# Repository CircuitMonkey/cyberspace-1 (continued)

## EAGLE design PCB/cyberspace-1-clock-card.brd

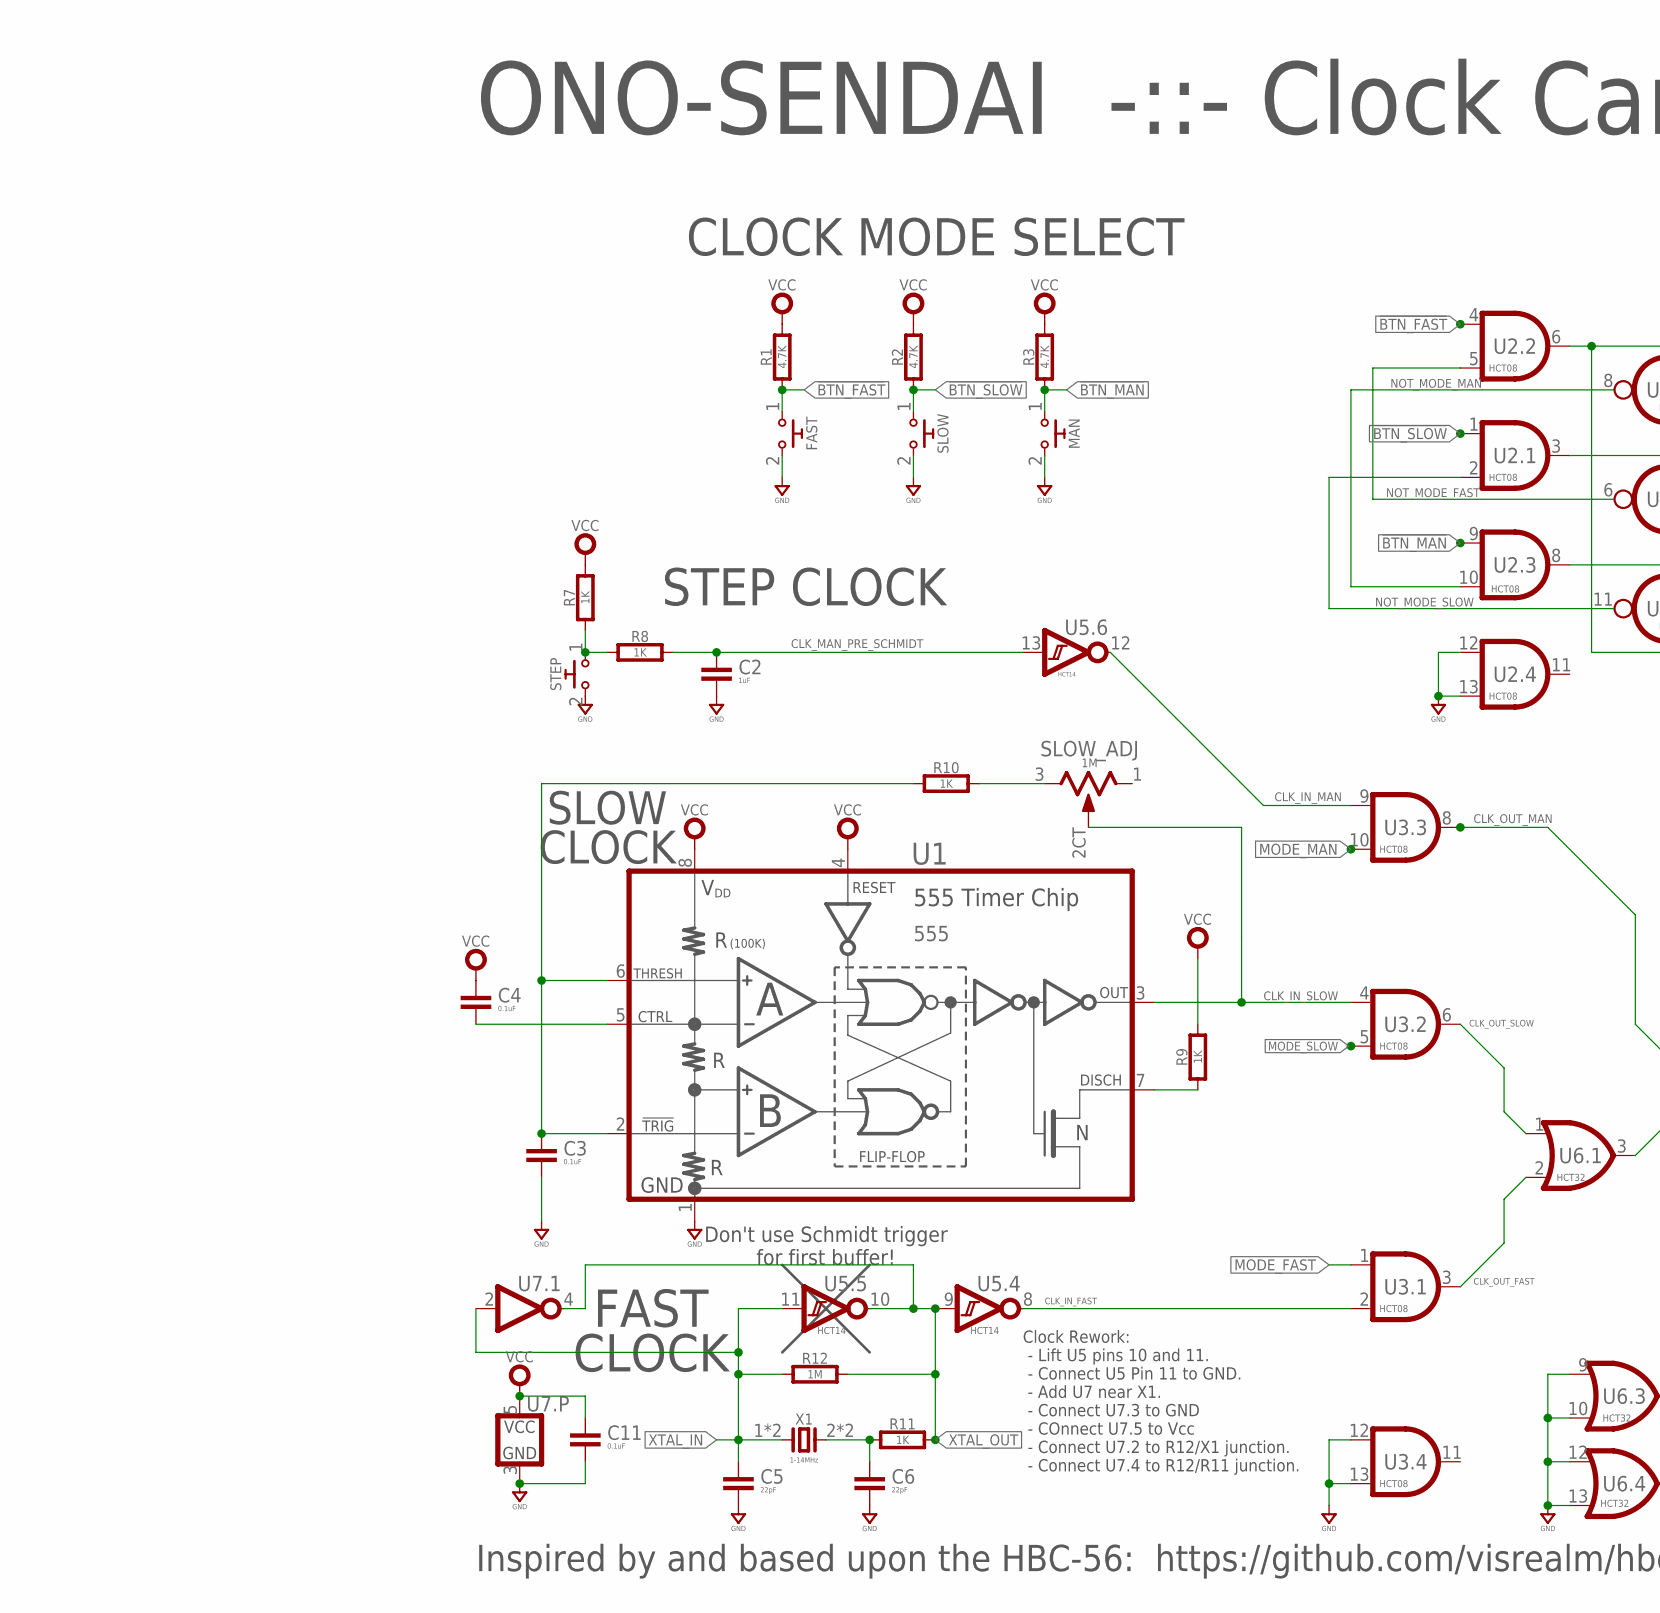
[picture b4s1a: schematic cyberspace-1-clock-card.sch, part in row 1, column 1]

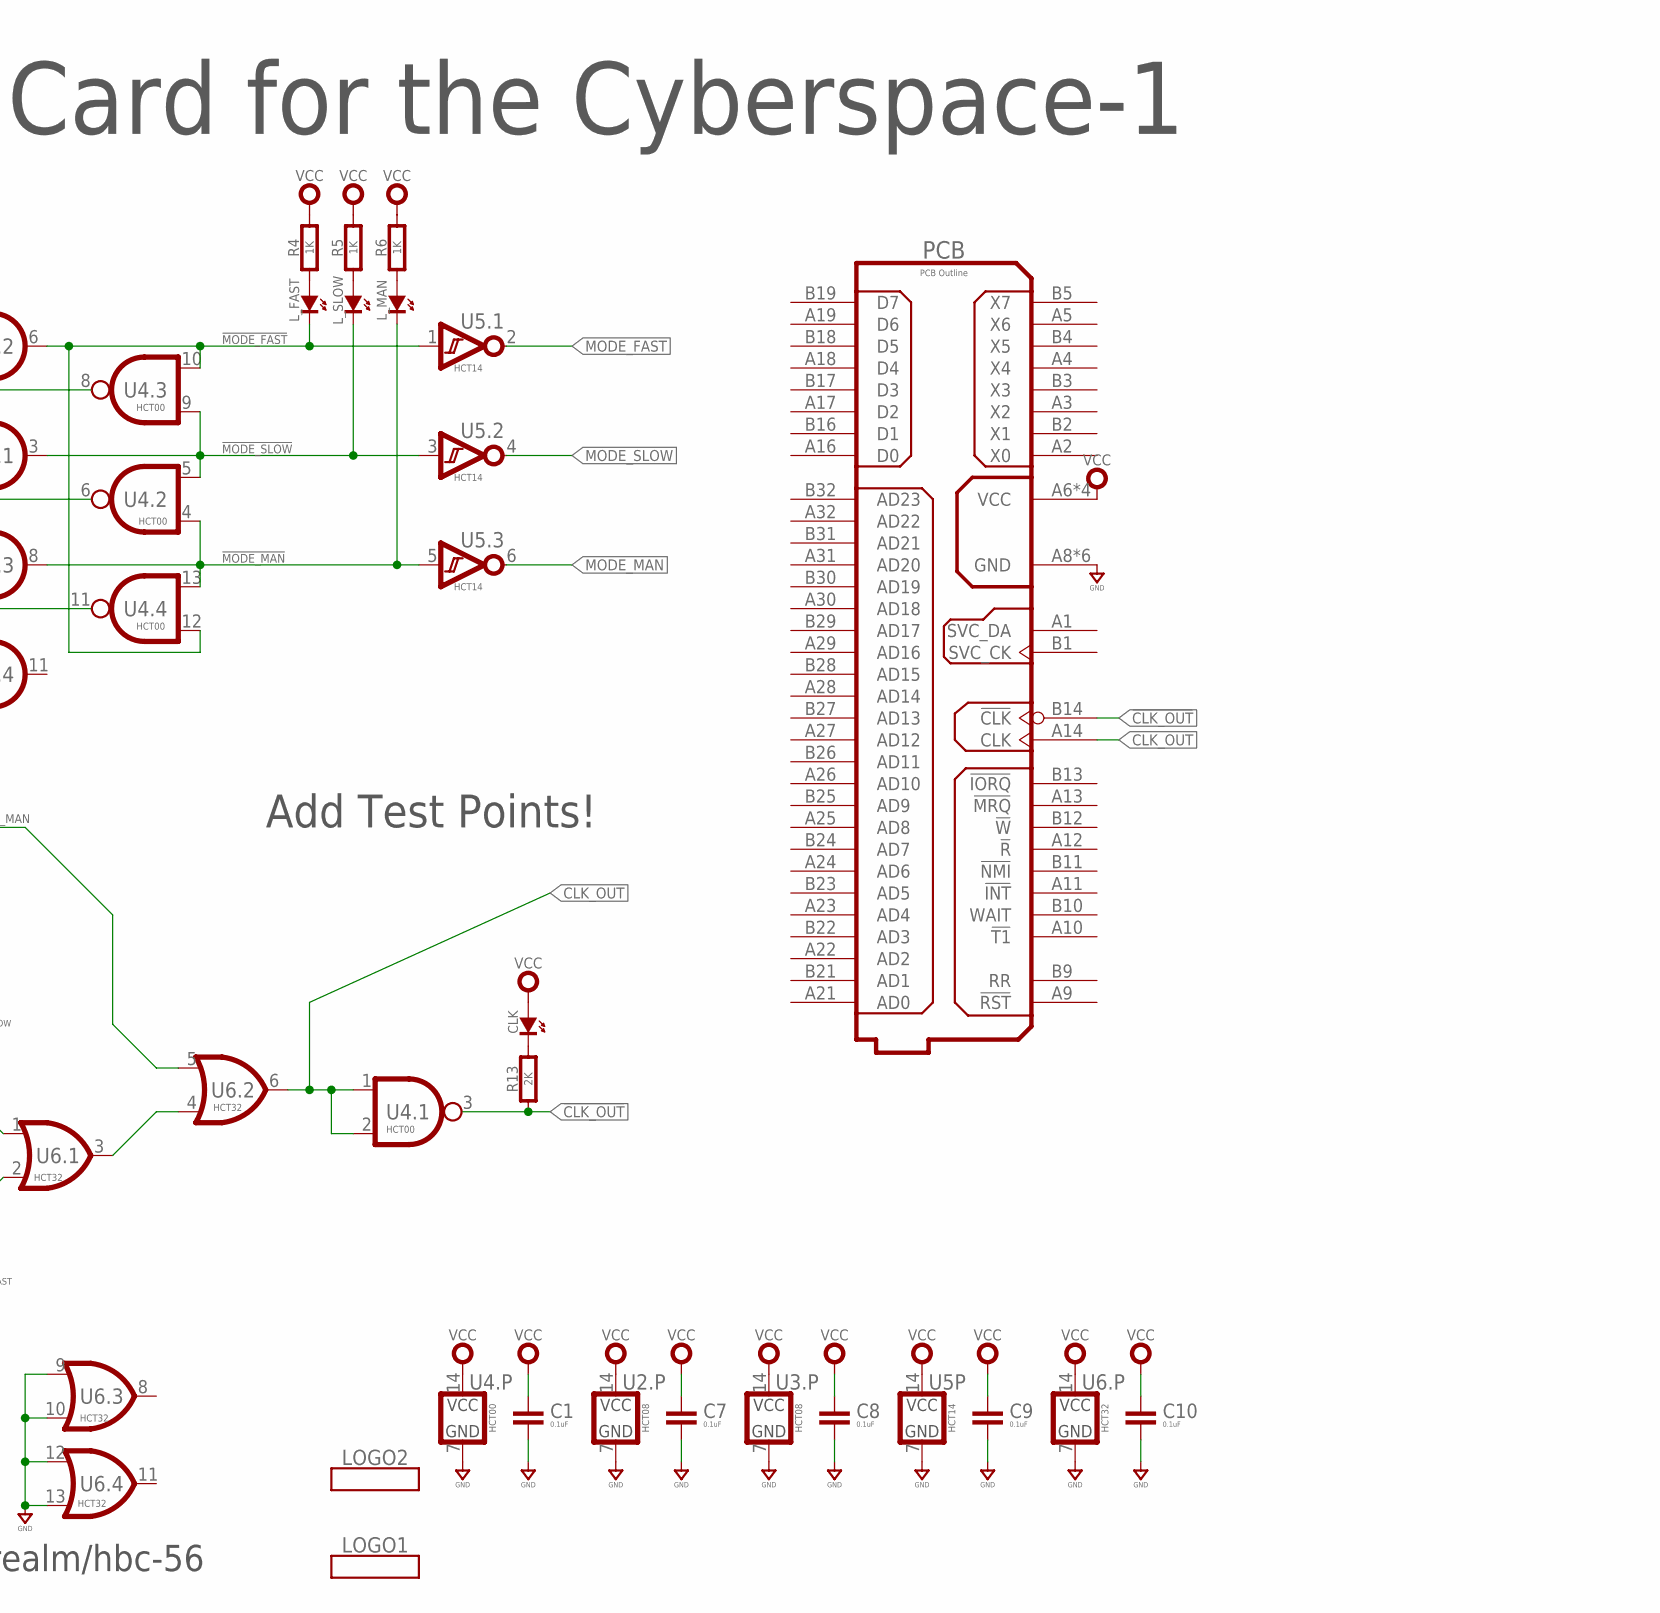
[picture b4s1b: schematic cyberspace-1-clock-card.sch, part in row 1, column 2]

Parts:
C1, C3, C4, C7, C8, C9, C10, C11: 0.1uF; 0603-CAP
C2: 1uF; 0603-CAP
C5, C6: 22pF; 0603-CAP
CLK: SMT0603; SMD_0603
FAST: TACTILESPST-RA-6X6; TC-0202
LOGO1: SOZU-BRAND-LOGO-20MM; SOZU-20MM
LOGO2: CHRONOS-LOGO-20MM; CHRONOS2-20MM
L_FAST: SMT0603; SMD_0603
L_MAN: SMT0603; SMD_0603
L_SLOW: SMT0603; SMD_0603
MAN: TACTILESPST-RA-6X6; TC-0202
PCB: PCB Outline; CYBERSPACE-CARD-TYPE-1A
R1, R2, R3: 4.7K; 0603-RES
R4, R5, R6, R7, R8, R9, R10, R11: 1K; 0603-RES
R12: 1M; 0603-RES
R13: 2K; 0603-RES
SLOW: TACTILESPST-RA-6X6; TC-0202
SLOW_ADJ: 1M; CERMET_MULTI_3006P_THD
STEP: TACTILESPST-RA-6X6; TC-0202
U1: 555; SOP08
U2, U3: HCT08; SOP14
U4: HCT00; SOP14
U5: HCT14; SOP14
U6: HCT32; SOP14
U7: 74HCT1G-TSOP504; TSOP-5
X1: 1-14MHz; ATSXXXX

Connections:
!BTN_FAST: FAST.1, R1.1, U2.4 (A)
!BTN_MAN: MAN.1, R3.1, U2.9 (A)
!BTN_SLOW: R2.1, SLOW.1, U2.1 (A)
!CLK_OUT: PCB.B14 (!CLK), R13.1, U4.3 (Y)
!MODE_FAST: L_FAST.K (C), U2.6 (Y), U4.10 (A), U4.12 (B), U5.1 (A)
!MODE_MAN: L_MAN.K (C), U2.8 (Y), U4.4 (A), U4.13 (A), U5.5 (A)
!MODE_SLOW: L_SLOW.K (C), U2.3 (Y), U4.5 (B), U4.9 (B), U5.3 (A)
CLK_IN_FAST: U3.2 (B), U5.8 (Y)
CLK_IN_MAN: U3.9 (A), U5.12 (Y)
CLK_IN_SLOW: SLOW_ADJ.2CT (2), U1.3 (OUTPUT), U3.4 (A)
CLK_MAN_PRE_SCHMIDT: C2.1, R8.2, U5.13 (A)
CLK_OUT: PCB.A14 (CLK), U4.1 (A), U4.2 (B), U6.6 (Y)
CLK_OUT_FAST: U3.3 (Y), U6.2 (B)
CLK_OUT_MAN: U3.8 (Y), U6.5 (B)
CLK_OUT_SLOW: U3.6 (Y), U6.1 (A)
GND: C1.2, C2.2, C3.2, C5.2, C6.2, C7.2, C8.2, C9.2, C10.2, C11.2, FAST.2, MAN.2, PCB.A8 (GND), PCB.A15 (GND), PCB.A20 (GND), PCB.B8 (GND), PCB.B15 (GND), PCB.B20 (GND), SLOW.2, STEP.2, U1.1 (GND), U2.7 (GND), U2.12 (A), U2.13 (B), U3.7 (GND), U3.12 (A), U3.13 (B), U4.7 (GND), U5.7 (GND), U6.7 (GND), U6.9 (A), U6.10 (B), U6.12 (A), U6.13 (B), U7.3 (GND)
MODE_FAST: U3.1 (A), U5.2 (Y)
MODE_MAN: U3.10 (B), U5.6 (Y)
MODE_SLOW: U3.5 (B), U5.4 (Y)
unnamed: C3.1, R10.1, U1.2 (TRIGGER#), U1.6 (THRESHOLD)
unnamed: R9.1, U1.7 (DISCHARGE)
unnamed: C4.2, U1.5 (CONTROL)
unnamed: C6.1, R11.1, X1.2, X1.2SMD
unnamed: R10.2, SLOW_ADJ.3
unnamed: U6.3 (Y), U6.4 (A)
unnamed: L_FAST.A, R4.1
unnamed: R7.1, R8.1, STEP.1
unnamed: L_SLOW.A, R5.1
unnamed: L_MAN.A, R6.1
unnamed: CLK.K (C), R13.2
NOT_MODE_FAST: U2.5 (B), U4.6 (Y)
NOT_MODE_MAN: U2.10 (B), U4.8 (Y)
NOT_MODE_SLOW: U2.2 (B), U4.11 (Y)
VCC: C1.1, C4.1, C7.1, C8.1, C9.1, C10.1, C11.1, CLK.A, PCB.A6 (VCC), PCB.A7 (VCC), PCB.B6 (VCC), PCB.B7 (VCC), R1.2, R2.2, R3.2, R4.2, R5.2, R6.2, R7.2, R9.2, U1.4 (RESET#), U1.8 (VDD), U2.14 (VCC), U3.14 (VCC), U4.14 (VCC), U5.14 (VCC), U6.14 (VCC), U7.5 (VCC)
XTAL_IN: C5.1, R12.1, U5.11 (A), U7.2 (A), X1.1, X1.1SMD
XTAL_OUT: R11.2, R12.2, U5.9 (A), U5.10 (Y), U7.4 (Y)

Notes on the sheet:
Inspired by and based upon the HBC-56: https://github.com/visrealm/hbc-56
ONO-SENDAI -::- Clock Card for the Cyberspace-1
FAST CLOCK
SLOW CLOCK
STEP CLOCK
CLOCK MODE SELECT
Add Test Points!
Don't use Schmidt trigger for first buffer!
Clock Rework: - Lift U5 pins 10 and 11. - Connect U5 Pin 11 to GND. - Add U7 near X1. - Connect U7.3 to GND - COnnect U7.5 to Vcc - Connect U7.2 to R12/X1 junction. - Connect U7.4 to R12/R11 junction.

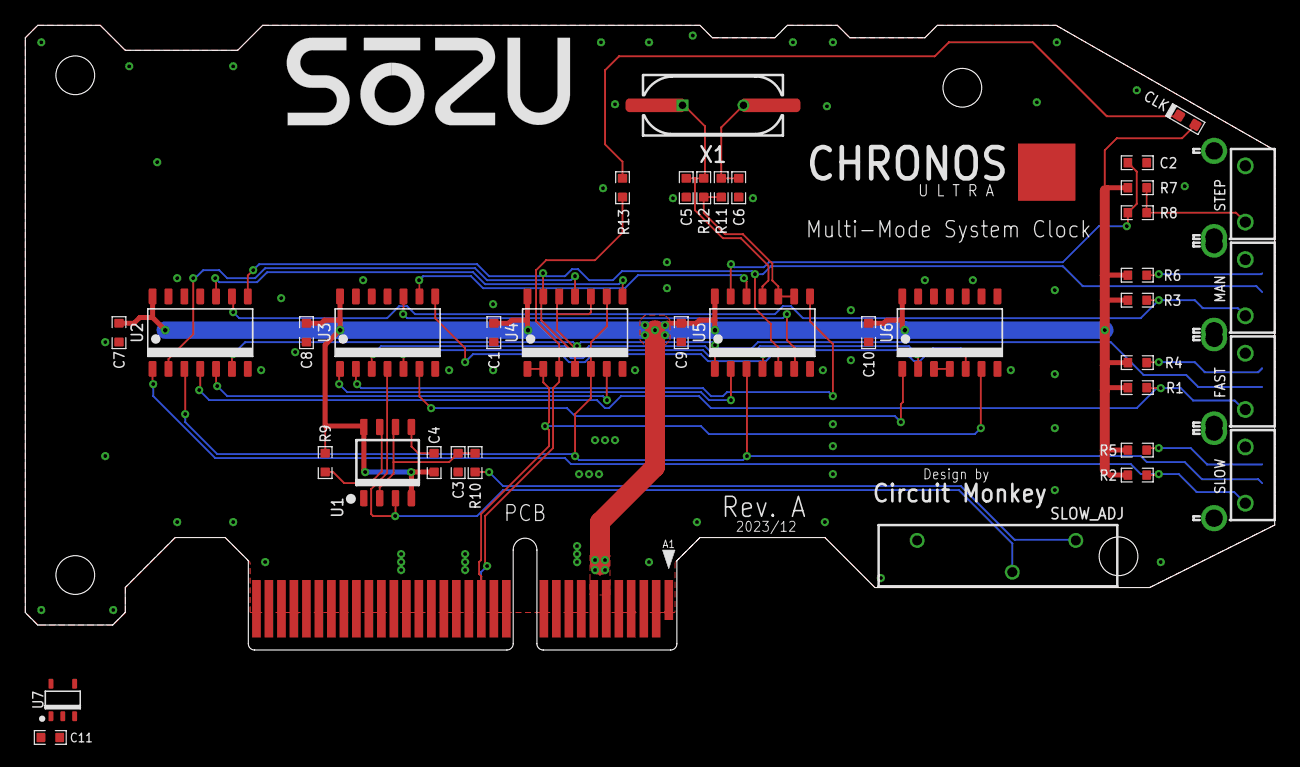
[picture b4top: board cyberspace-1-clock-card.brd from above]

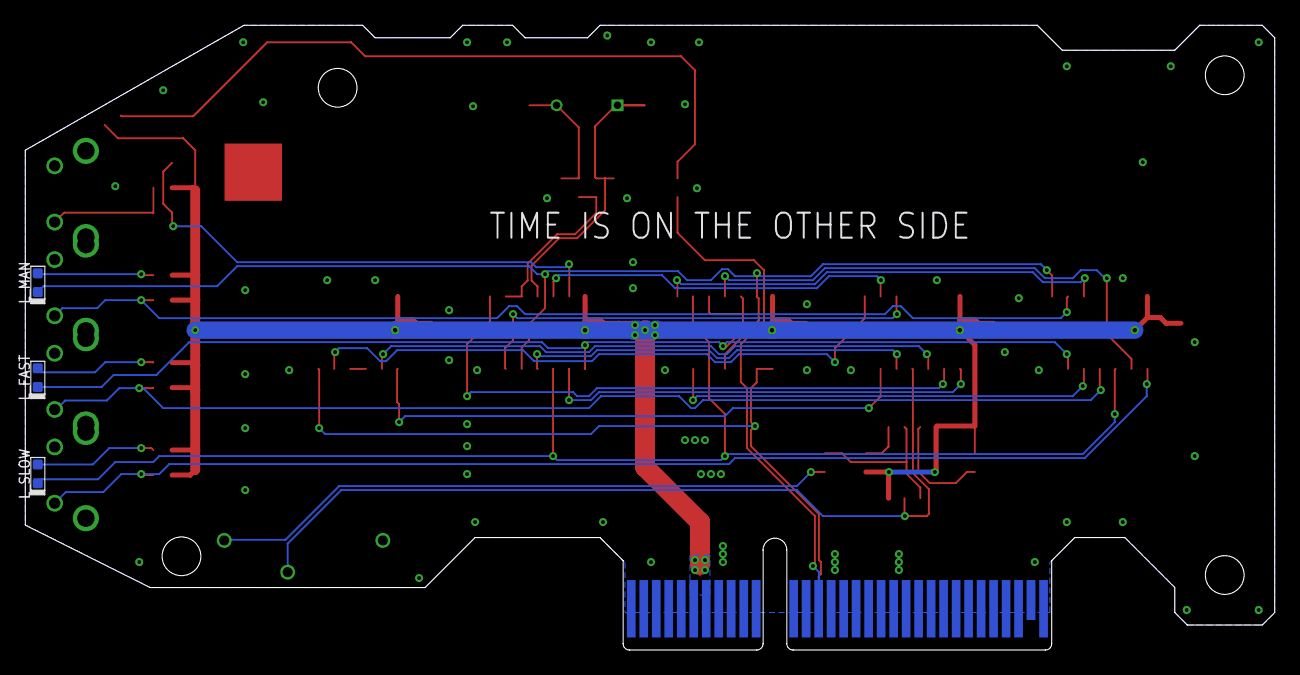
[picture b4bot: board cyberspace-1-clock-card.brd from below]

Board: 2 copper layers, 100.0 x 50.0 mm, 44 parts (3 on the bottom side), 36 nets.

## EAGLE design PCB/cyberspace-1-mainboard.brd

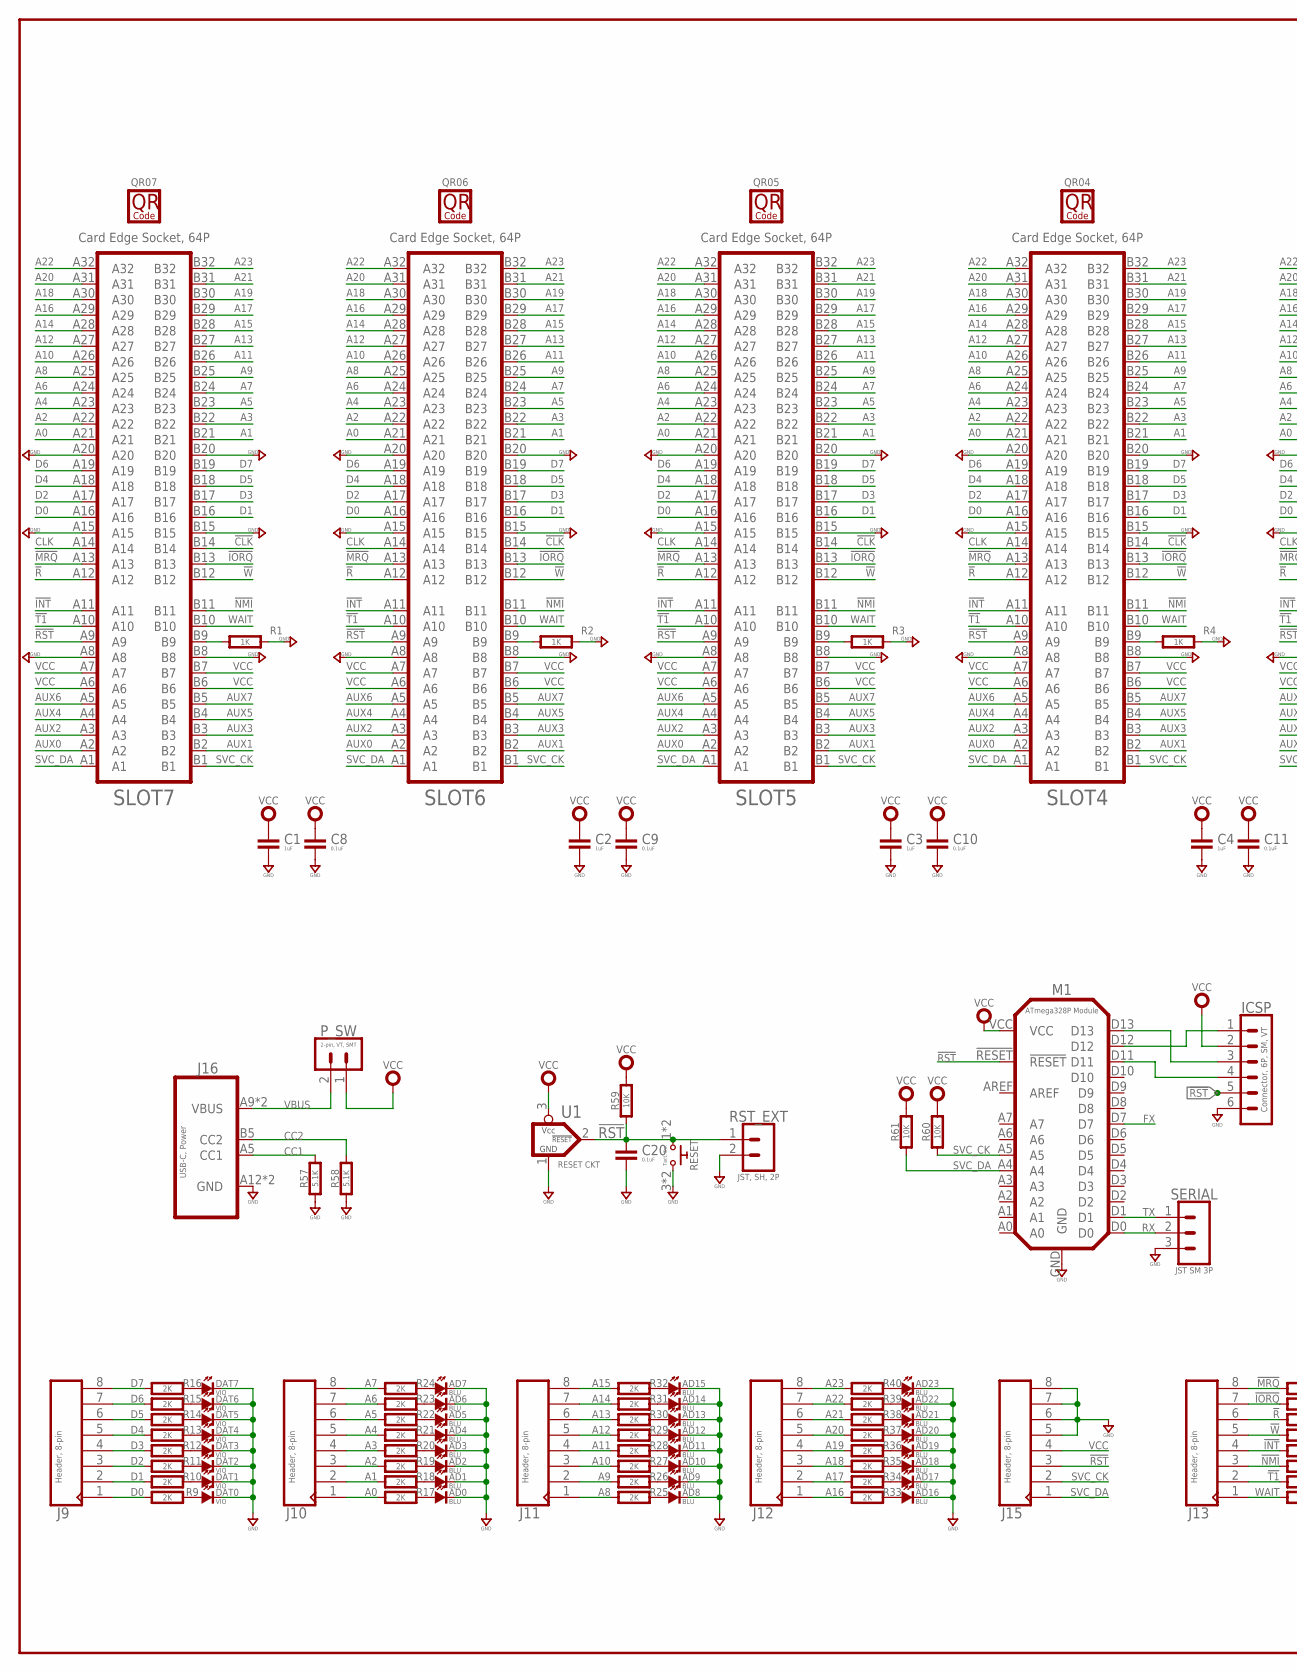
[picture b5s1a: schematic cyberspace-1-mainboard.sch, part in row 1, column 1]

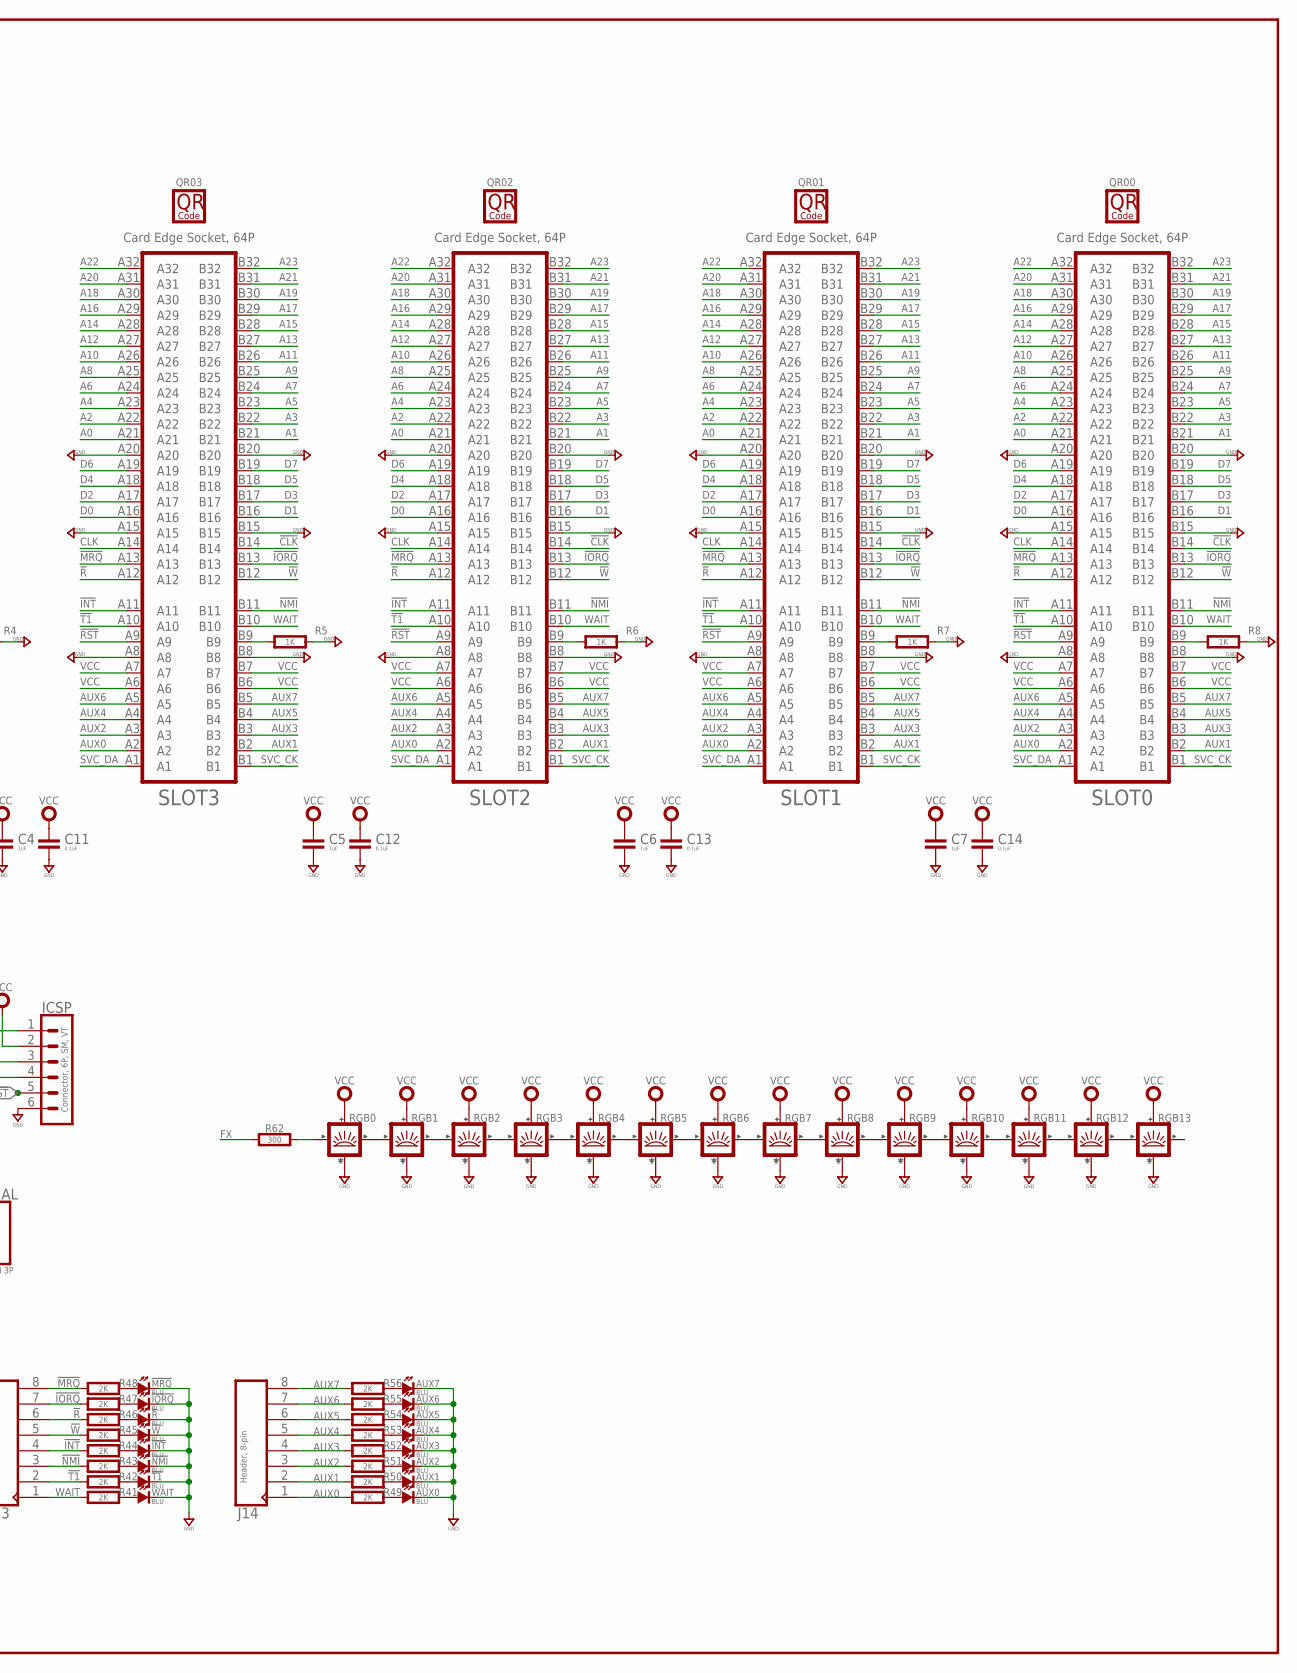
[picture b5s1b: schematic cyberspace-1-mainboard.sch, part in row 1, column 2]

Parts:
!INT: BLU; SMD_0603
!IORQ: BLU; SMD_0603
!MRQ: BLU; SMD_0603
!NMI: BLU; SMD_0603
!R: BLU; SMD_0603
!T1: BLU; SMD_0603
!W: BLU; SMD_0603
AD0, AD1, AD2, AD3, AD4, AD5, AD6, AD7, AD8, AD9, AD10, AD11, AD12, AD13, AD14, AD15, AD16, AD17, AD18, AD19, AD20, AD21, AD22, AD23: BLU; SMD_0603
AUX0, AUX1, AUX2, AUX3, AUX4, AUX5, AUX6, AUX7: BLU; SMD_0603
C1, C2, C3, C4, C5, C6, C7: 1uF; 0603-CAP
C8, C9, C10, C11, C12, C13, C14, C20: 0.1uF; 0603-CAP
DAT0, DAT1, DAT2, DAT3, DAT4, DAT5, DAT6, DAT7: VIO; SMD_0603
ICSP: Connector, 6P, SM, VT; BM06B-SRSS-TB
J9, J10, J11, J12, J13, J14, J15: Header, 8-pin; MA08X1-VT-THD
J16: USB-C, Power; GCT-USB4125
M1: ATmega328P Module; 0119A
P_SW: 2-pin, VT, SMT; B2B-PH-SM4
QR00: QR_CODE-00-7MM; QR-7MM-00
QR01: QR_CODE-01-7MM; QR-7MM-01
QR02: QR_CODE-02-7MM; QR-7MM-02
QR03: QR_CODE-03-7MM; QR-7MM-03
QR04: QR_CODE-04-7MM; QR-7MM-04
QR05: QR_CODE-05-7MM; QR-7MM-05
QR06: QR_CODE-06-7MM; QR-7MM-06
QR07: QR_CODE-07-7MM; QR-7MM-07
R1, R2, R3, R4, R5, R6, R7, R8: 1K; 0603-RES
R9, R10, R11, R12, R13, R14, R15, R16, R17, R18, R19, R20, R21, R22, R23, R24, R25, R26, R27, R28, R29, R30, R31, R32, R33, R34, R35, R36, R37, R38, R39, R40, R41, R42, R43, R44, R45, R46, R47, R48, R49, R50, R51, R52, R53, R54, R55, R56: 2K; 0603-RES
R57, R58: 5.1K; 0603-RES
R59, R60, R61: 10K; 0603-RES
R62: 300; 0603-RES
RESET: Tact. Sw.; B3FS
RGB0, RGB1, RGB2, RGB3, RGB4, RGB5, RGB6, RGB7, RGB8, RGB9, RGB10, RGB11, RGB12, RGB13: SMART_LED4020-SIDE; SMD_4020
RST_EXT: JST, SH, 2P; BM02B-SRSS-TB
SERIAL: JST SM 3P; BM03B-SRSS-TB
SLOT0, SLOT1, SLOT2, SLOT3, SLOT4, SLOT5, SLOT6, SLOT7: Card Edge Socket, 64P; PCIE-64P-SOCKET
U1: RESET CKT; SOT-23
WAIT: BLU; SMD_0603

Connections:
!CLK: SLOT0.B14, SLOT1.B14, SLOT2.B14, SLOT3.B14, SLOT4.B14, SLOT5.B14, SLOT6.B14, SLOT7.B14
!INT: J13.4, R44.1, SLOT0.A11, SLOT1.A11, SLOT2.A11, SLOT3.A11, SLOT4.A11, SLOT5.A11, SLOT6.A11, SLOT7.A11
!IORQ: J13.7, R47.1, SLOT0.B13, SLOT1.B13, SLOT2.B13, SLOT3.B13, SLOT4.B13, SLOT5.B13, SLOT6.B13, SLOT7.B13
!MRQ: J13.8, R48.1, SLOT0.A13, SLOT1.A13, SLOT2.A13, SLOT3.A13, SLOT4.A13, SLOT5.A13, SLOT6.A13, SLOT7.A13
!NMI: J13.3, R43.1, SLOT0.B11, SLOT1.B11, SLOT2.B11, SLOT3.B11, SLOT4.B11, SLOT5.B11, SLOT6.B11, SLOT7.B11
!R: J13.6, R46.1, SLOT0.A12, SLOT1.A12, SLOT2.A12, SLOT3.A12, SLOT4.A12, SLOT5.A12, SLOT6.A12, SLOT7.A12
!RST: C20.1, ICSP.5, J15.3, M1.!RESET, R59.1, RESET.1, RESET.2 (1), RST_EXT.1, SLOT0.A9, SLOT1.A9, SLOT2.A9, SLOT3.A9, SLOT4.A9, SLOT5.A9, SLOT6.A9, SLOT7.A9, U1.2 (!RST)
!T1: J13.2, R42.1, SLOT0.A10, SLOT1.A10, SLOT2.A10, SLOT3.A10, SLOT4.A10, SLOT5.A10, SLOT6.A10, SLOT7.A10
!W: J13.5, R45.1, SLOT0.B12, SLOT1.B12, SLOT2.B12, SLOT3.B12, SLOT4.B12, SLOT5.B12, SLOT6.B12, SLOT7.B12
A0: J10.1, R17.1, SLOT0.A21, SLOT1.A21, SLOT2.A21, SLOT3.A21, SLOT4.A21, SLOT5.A21, SLOT6.A21, SLOT7.A21
A1: J10.2, R18.1, SLOT0.B21, SLOT1.B21, SLOT2.B21, SLOT3.B21, SLOT4.B21, SLOT5.B21, SLOT6.B21, SLOT7.B21
A2: J10.3, R19.1, SLOT0.A22, SLOT1.A22, SLOT2.A22, SLOT3.A22, SLOT4.A22, SLOT5.A22, SLOT6.A22, SLOT7.A22
A3: J10.4, R20.1, SLOT0.B22, SLOT1.B22, SLOT2.B22, SLOT3.B22, SLOT4.B22, SLOT5.B22, SLOT6.B22, SLOT7.B22
A4: J10.5, R21.1, SLOT0.A23, SLOT1.A23, SLOT2.A23, SLOT3.A23, SLOT4.A23, SLOT5.A23, SLOT6.A23, SLOT7.A23
A5: J10.6, R22.1, SLOT0.B23, SLOT1.B23, SLOT2.B23, SLOT3.B23, SLOT4.B23, SLOT5.B23, SLOT6.B23, SLOT7.B23
A6: J10.7, R23.1, SLOT0.A24, SLOT1.A24, SLOT2.A24, SLOT3.A24, SLOT4.A24, SLOT5.A24, SLOT6.A24, SLOT7.A24
A7: J10.8, R24.1, SLOT0.B24, SLOT1.B24, SLOT2.B24, SLOT3.B24, SLOT4.B24, SLOT5.B24, SLOT6.B24, SLOT7.B24
A8: J11.1, R25.1, SLOT0.A25, SLOT1.A25, SLOT2.A25, SLOT3.A25, SLOT4.A25, SLOT5.A25, SLOT6.A25, SLOT7.A25
A9: J11.2, R26.1, SLOT0.B25, SLOT1.B25, SLOT2.B25, SLOT3.B25, SLOT4.B25, SLOT5.B25, SLOT6.B25, SLOT7.B25
A10: J11.3, R27.1, SLOT0.A26, SLOT1.A26, SLOT2.A26, SLOT3.A26, SLOT4.A26, SLOT5.A26, SLOT6.A26, SLOT7.A26
A11: J11.4, R28.1, SLOT0.B26, SLOT1.B26, SLOT2.B26, SLOT3.B26, SLOT4.B26, SLOT5.B26, SLOT6.B26, SLOT7.B26
A12: J11.5, R29.1, SLOT0.A27, SLOT1.A27, SLOT2.A27, SLOT3.A27, SLOT4.A27, SLOT5.A27, SLOT6.A27, SLOT7.A27
A13: J11.6, R30.1, SLOT0.B27, SLOT1.B27, SLOT2.B27, SLOT3.B27, SLOT4.B27, SLOT5.B27, SLOT6.B27, SLOT7.B27
A14: J11.7, R31.1, SLOT0.A28, SLOT1.A28, SLOT2.A28, SLOT3.A28, SLOT4.A28, SLOT5.A28, SLOT6.A28, SLOT7.A28
A15: J11.8, R32.1, SLOT0.B28, SLOT1.B28, SLOT2.B28, SLOT3.B28, SLOT4.B28, SLOT5.B28, SLOT6.B28, SLOT7.B28
A16: J12.1, R33.1, SLOT0.A29, SLOT1.A29, SLOT2.A29, SLOT3.A29, SLOT4.A29, SLOT5.A29, SLOT6.A29, SLOT7.A29
A17: J12.2, R34.1, SLOT0.B29, SLOT1.B29, SLOT2.B29, SLOT3.B29, SLOT4.B29, SLOT5.B29, SLOT6.B29, SLOT7.B29
A18: J12.3, R35.1, SLOT0.A30, SLOT1.A30, SLOT2.A30, SLOT3.A30, SLOT4.A30, SLOT5.A30, SLOT6.A30, SLOT7.A30
A19: J12.4, R36.1, SLOT0.B30, SLOT1.B30, SLOT2.B30, SLOT3.B30, SLOT4.B30, SLOT5.B30, SLOT6.B30, SLOT7.B30
A20: J12.5, R37.1, SLOT0.A31, SLOT1.A31, SLOT2.A31, SLOT3.A31, SLOT4.A31, SLOT5.A31, SLOT6.A31, SLOT7.A31
A21: J12.6, R38.1, SLOT0.B31, SLOT1.B31, SLOT2.B31, SLOT3.B31, SLOT4.B31, SLOT5.B31, SLOT6.B31, SLOT7.B31
A22: J12.7, R39.1, SLOT0.A32, SLOT1.A32, SLOT2.A32, SLOT3.A32, SLOT4.A32, SLOT5.A32, SLOT6.A32, SLOT7.A32
A23: J12.8, R40.1, SLOT0.B32, SLOT1.B32, SLOT2.B32, SLOT3.B32, SLOT4.B32, SLOT5.B32, SLOT6.B32, SLOT7.B32
AUX0: J14.1, R49.1, SLOT0.A2, SLOT1.A2, SLOT2.A2, SLOT3.A2, SLOT4.A2, SLOT5.A2, SLOT6.A2, SLOT7.A2
AUX1: J14.2, R50.1, SLOT0.B2, SLOT1.B2, SLOT2.B2, SLOT3.B2, SLOT4.B2, SLOT5.B2, SLOT6.B2, SLOT7.B2
AUX2: J14.3, R51.1, SLOT0.A3, SLOT1.A3, SLOT2.A3, SLOT3.A3, SLOT4.A3, SLOT5.A3, SLOT6.A3, SLOT7.A3
AUX3: J14.4, R52.1, SLOT0.B3, SLOT1.B3, SLOT2.B3, SLOT3.B3, SLOT4.B3, SLOT5.B3, SLOT6.B3, SLOT7.B3
AUX4: J14.5, R53.1, SLOT0.A4, SLOT1.A4, SLOT2.A4, SLOT3.A4, SLOT4.A4, SLOT5.A4, SLOT6.A4, SLOT7.A4
AUX5: J14.6, R54.1, SLOT0.B4, SLOT1.B4, SLOT2.B4, SLOT3.B4, SLOT4.B4, SLOT5.B4, SLOT6.B4, SLOT7.B4
AUX6: J14.7, R55.1, SLOT0.A5, SLOT1.A5, SLOT2.A5, SLOT3.A5, SLOT4.A5, SLOT5.A5, SLOT6.A5, SLOT7.A5
AUX7: J14.8, R56.1, SLOT0.B5, SLOT1.B5, SLOT2.B5, SLOT3.B5, SLOT4.B5, SLOT5.B5, SLOT6.B5, SLOT7.B5
CC1: J16.A5 (CC1), R57.2
CC2: J16.B5 (CC2), R58.2
CLK: SLOT0.A14, SLOT1.A14, SLOT2.A14, SLOT3.A14, SLOT4.A14, SLOT5.A14, SLOT6.A14, SLOT7.A14
D0: J9.1, R9.1, SLOT0.A16, SLOT1.A16, SLOT2.A16, SLOT3.A16, SLOT4.A16, SLOT5.A16, SLOT6.A16, SLOT7.A16
D1: J9.2, R10.1, SLOT0.B16, SLOT1.B16, SLOT2.B16, SLOT3.B16, SLOT4.B16, SLOT5.B16, SLOT6.B16, SLOT7.B16
D2: J9.3, R11.1, SLOT0.A17, SLOT1.A17, SLOT2.A17, SLOT3.A17, SLOT4.A17, SLOT5.A17, SLOT6.A17, SLOT7.A17
D3: J9.4, R12.1, SLOT0.B17, SLOT1.B17, SLOT2.B17, SLOT3.B17, SLOT4.B17, SLOT5.B17, SLOT6.B17, SLOT7.B17
D4: J9.5, R13.1, SLOT0.A18, SLOT1.A18, SLOT2.A18, SLOT3.A18, SLOT4.A18, SLOT5.A18, SLOT6.A18, SLOT7.A18
D5: J9.6, R14.1, SLOT0.B18, SLOT1.B18, SLOT2.B18, SLOT3.B18, SLOT4.B18, SLOT5.B18, SLOT6.B18, SLOT7.B18
D6: J9.7, R15.1, SLOT0.A19, SLOT1.A19, SLOT2.A19, SLOT3.A19, SLOT4.A19, SLOT5.A19, SLOT6.A19, SLOT7.A19
D7: J9.8, R16.1, SLOT0.B19, SLOT1.B19, SLOT2.B19, SLOT3.B19, SLOT4.B19, SLOT5.B19, SLOT6.B19, SLOT7.B19
FX: M1.D7, R62.1
GND: !INT.K (C), !IORQ.K (C), !MRQ.K (C), !NMI.K (C), !R.K (C), !T1.K (C), !W.K (C), AD0.K (C), AD1.K (C), AD2.K (C), AD3.K (C), AD4.K (C), AD5.K (C), AD6.K (C), AD7.K (C), AD8.K (C), AD9.K (C), AD10.K (C), AD11.K (C), AD12.K (C), AD13.K (C), AD14.K (C), AD15.K (C), AD16.K (C), AD17.K (C), AD18.K (C), AD19.K (C), AD20.K (C), AD21.K (C), AD22.K (C), AD23.K (C), AUX0.K (C), AUX1.K (C), AUX2.K (C), AUX3.K (C), AUX4.K (C), AUX5.K (C), AUX6.K (C), AUX7.K (C), C1.2, C2.2, C3.2, C4.2, C5.2, C6.2, C7.2, C8.2, C9.2, C10.2, C11.2, C12.2, C13.2, C14.2, C20.2, DAT0.K (C), DAT1.K (C), DAT2.K (C), DAT3.K (C), DAT4.K (C), DAT5.K (C), DAT6.K (C), DAT7.K (C), ICSP.6, J15.5, J15.6, J15.7, J15.8, J16.A12 (GND), J16.B12 (GND), M1.GND, R1.2, R2.2, R3.2, R4.2, R5.2, R6.2, R7.2, R8.2, R57.1, R58.1, RESET.3 (2), RESET.4 (2), RGB0.4 (GND), RGB1.4 (GND), RGB2.4 (GND), RGB3.4 (GND), RGB4.4 (GND), RGB5.4 (GND), RGB6.4 (GND), RGB7.4 (GND), RGB8.4 (GND), RGB9.4 (GND), RGB10.4 (GND), RGB11.4 (GND), RGB12.4 (GND), RGB13.4 (GND), RST_EXT.2, SERIAL.3, SLOT0.A8, SLOT0.A15, SLOT0.A20, SLOT0.B8, SLOT0.B15, SLOT0.B20, SLOT1.A8, SLOT1.A15, SLOT1.A20, SLOT1.B8, SLOT1.B15, SLOT1.B20, SLOT2.A8, SLOT2.A15, SLOT2.A20, SLOT2.B8, SLOT2.B15, SLOT2.B20, SLOT3.A8, SLOT3.A15, SLOT3.A20, SLOT3.B8, SLOT3.B15, SLOT3.B20, SLOT4.A8, SLOT4.A15, SLOT4.A20, SLOT4.B8, SLOT4.B15, SLOT4.B20, SLOT5.A8, SLOT5.A15, SLOT5.A20, SLOT5.B8, SLOT5.B15, SLOT5.B20, SLOT6.A8, SLOT6.A15, SLOT6.A20, SLOT6.B8, SLOT6.B15, SLOT6.B20, SLOT7.A8, SLOT7.A15, SLOT7.A20, SLOT7.B8, SLOT7.B15, SLOT7.B20, U1.1 (GND), WAIT.K (C)
MISO: ICSP.1, M1.D12
MOSI: ICSP.4, M1.D11
unnamed: R1.1, SLOT7.B9
unnamed: DAT0.A, R9.2
unnamed: DAT1.A, R10.2
unnamed: DAT2.A, R11.2
unnamed: DAT3.A, R12.2
unnamed: DAT4.A, R13.2
unnamed: DAT5.A, R14.2
unnamed: DAT6.A, R15.2
unnamed: R2.1, SLOT6.B9
unnamed: DAT7.A, R16.2
unnamed: R3.1, SLOT5.B9
unnamed: AD0.A, R17.2
unnamed: R4.1, SLOT4.B9
unnamed: AD1.A, R18.2
unnamed: R5.1, SLOT3.B9
unnamed: AD2.A, R19.2
unnamed: R6.1, SLOT2.B9
unnamed: AD3.A, R20.2
unnamed: R7.1, SLOT1.B9
unnamed: AD4.A, R21.2
unnamed: R8.1, SLOT0.B9
unnamed: AD5.A, R22.2
unnamed: AD6.A, R23.2
unnamed: AD7.A, R24.2
unnamed: AD8.A, R25.2
unnamed: AD9.A, R26.2
unnamed: AD10.A, R27.2
unnamed: AD11.A, R28.2
unnamed: AD12.A, R29.2
unnamed: AD13.A, R30.2
unnamed: AD14.A, R31.2
unnamed: AD15.A, R32.2
unnamed: AD16.A, R33.2
unnamed: AD17.A, R34.2
unnamed: AD18.A, R35.2
unnamed: AD19.A, R36.2
unnamed: AD20.A, R37.2
unnamed: AD21.A, R38.2
unnamed: AD22.A, R39.2
unnamed: AD23.A, R40.2
unnamed: R41.2, WAIT.A
unnamed: !T1.A, R42.2
unnamed: !NMI.A, R43.2
unnamed: !INT.A, R44.2
unnamed: !W.A, R45.2
unnamed: !R.A, R46.2
unnamed: !IORQ.A, R47.2
unnamed: !MRQ.A, R48.2
unnamed: AUX0.A, R49.2
unnamed: AUX1.A, R50.2
unnamed: AUX2.A, R51.2
unnamed: AUX3.A, R52.2
unnamed: AUX4.A, R53.2
unnamed: AUX5.A, R54.2
unnamed: AUX6.A, R55.2
unnamed: AUX7.A, R56.2
unnamed: RGB0.3 (OUT), RGB1.1 (IN)
unnamed: RGB1.3 (OUT), RGB2.1 (IN)
unnamed: RGB2.3 (OUT), RGB3.1 (IN)
unnamed: RGB3.3 (OUT), RGB4.1 (IN)
unnamed: RGB4.3 (OUT), RGB5.1 (IN)
unnamed: RGB5.3 (OUT), RGB6.1 (IN)
unnamed: RGB6.3 (OUT), RGB7.1 (IN)
unnamed: RGB7.3 (OUT), RGB8.1 (IN)
unnamed: RGB8.3 (OUT), RGB9.1 (IN)
unnamed: RGB9.3 (OUT), RGB10.1 (IN)
unnamed: RGB10.3 (OUT), RGB11.1 (IN)
unnamed: RGB11.3 (OUT), RGB12.1 (IN)
unnamed: RGB12.3 (OUT), RGB13.1 (IN)
unnamed: R62.2, RGB0.1 (IN)
RX: M1.D0, SERIAL.2
SCK: ICSP.3, M1.D13
SVC_CK: J15.2, M1.A5, R60.1, SLOT0.B1, SLOT1.B1, SLOT2.B1, SLOT3.B1, SLOT4.B1, SLOT5.B1, SLOT6.B1, SLOT7.B1
SVC_DA: J15.1, M1.A4, R61.1, SLOT0.A1, SLOT1.A1, SLOT2.A1, SLOT3.A1, SLOT4.A1, SLOT5.A1, SLOT6.A1, SLOT7.A1
TX: M1.D1, SERIAL.1
VBUS: J16.A9 (VBUS), J16.B9 (VBUS), P_SW.2
VCC: C1.1, C2.1, C3.1, C4.1, C5.1, C6.1, C7.1, C8.1, C9.1, C10.1, C11.1, C12.1, C13.1, C14.1, ICSP.2, J15.4, M1.VCC, P_SW.1, R59.2, R60.2, R61.2, RGB0.2 (VDD), RGB1.2 (VDD), RGB2.2 (VDD), RGB3.2 (VDD), RGB4.2 (VDD), RGB5.2 (VDD), RGB6.2 (VDD), RGB7.2 (VDD), RGB8.2 (VDD), RGB9.2 (VDD), RGB10.2 (VDD), RGB11.2 (VDD), RGB12.2 (VDD), RGB13.2 (VDD), SLOT0.A6, SLOT0.A7, SLOT0.B6, SLOT0.B7, SLOT1.A6, SLOT1.A7, SLOT1.B6, SLOT1.B7, SLOT2.A6, SLOT2.A7, SLOT2.B6, SLOT2.B7, SLOT3.A6, SLOT3.A7, SLOT3.B6, SLOT3.B7, SLOT4.A6, SLOT4.A7, SLOT4.B6, SLOT4.B7, SLOT5.A6, SLOT5.A7, SLOT5.B6, SLOT5.B7, SLOT6.A6, SLOT6.A7, SLOT6.B6, SLOT6.B7, SLOT7.A6, SLOT7.A7, SLOT7.B6, SLOT7.B7, U1.3 (VCC)
WAIT: J13.1, R41.1, SLOT0.B10, SLOT1.B10, SLOT2.B10, SLOT3.B10, SLOT4.B10, SLOT5.B10, SLOT6.B10, SLOT7.B10

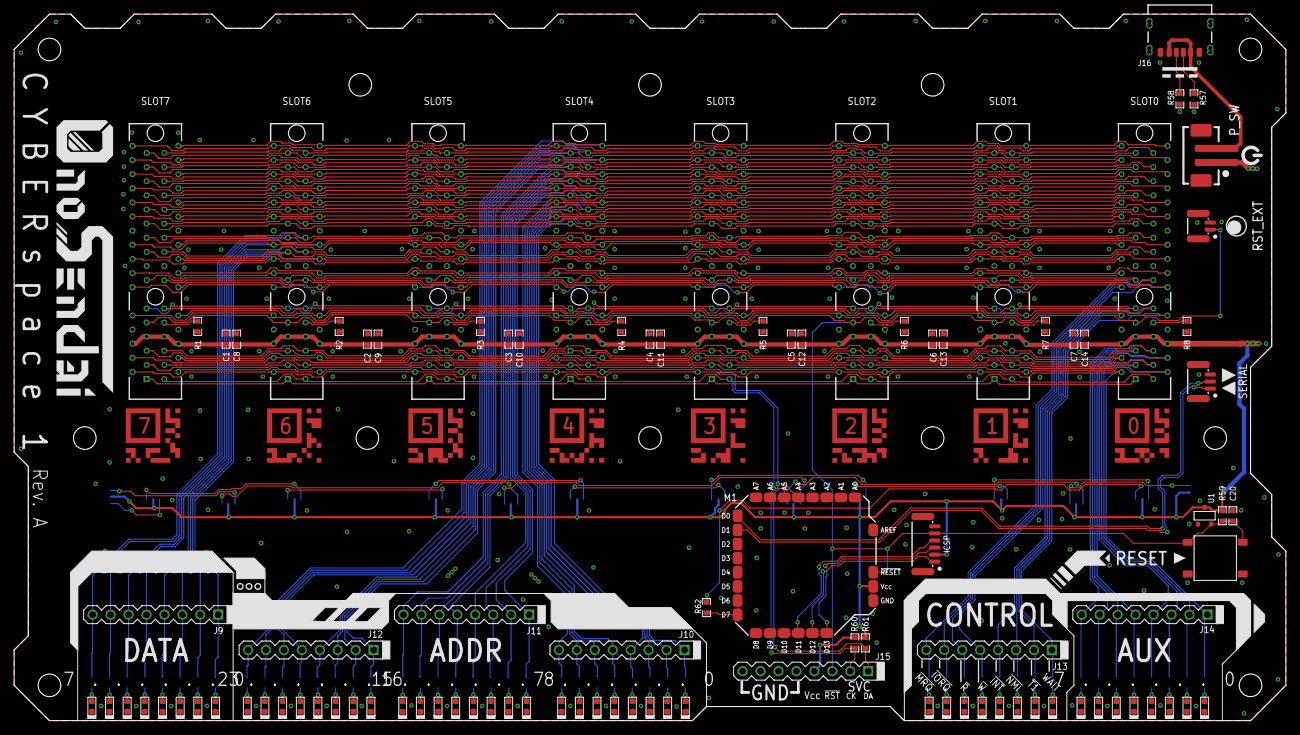
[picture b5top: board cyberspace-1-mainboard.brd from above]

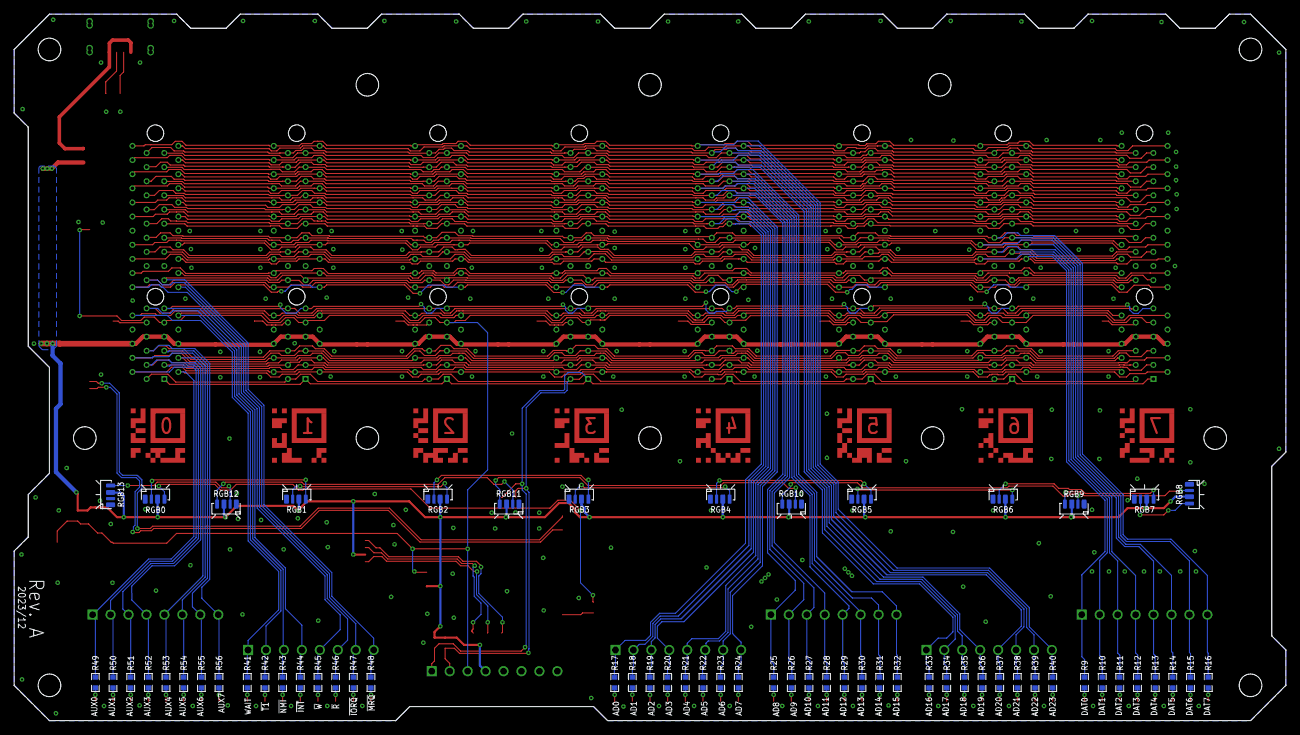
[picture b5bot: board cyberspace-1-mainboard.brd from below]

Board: 2 copper layers, 180.0 x 100.0 mm, 170 parts (62 on the bottom side), 134 nets.
